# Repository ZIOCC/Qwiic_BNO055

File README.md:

# Zio Qwiic 9DOF IMU BNO055

> This product can be available for purchase [here](https://www.smart-prototyping.com/Zio-9DOF-IMU-BNO055.html).

#### Description

The BNO055 is the ideal orientation solution with low overhead. What that means is that the computational cost is incredibly low for such a high-powered sensor. So, if you have a project consisting of peripherals that demand more computational power, the BNO055 is a great IMU to incorporate.

It provides Absolute Orientation by integrating 3 different sensors: a 3-axis 14-bit accelerometer,  3-axis 16-bit gyroscope, and a 3-axis magnetometer; and outputting the fused data in usable values. 

The following data can be collected by this sensor:

* **Quaternion Absolute Orientation** (4-point quaternion output that is as fast as it is sexy… that’s right, quaternions are sexy.)
* Euler Vector Absolute Orientation ( 3-axis orientation data based on a 360 sphere)
* Linear Acceleration in m/s^2
* Acceleration Vector  in m/s^2
* Magnetic Field Strength Vector
* Gravity Vector
* Angular Velocity Vector
* Temperature

We’ve made this board small enough to be suitable for use in advanced wearables and other space-sensitive projects. It’s been specifically designed for use in projects incorporating Qwiic, and so breaks out only the interrupt pin. However, if you’d like to use it in a non-Qwiic project, just use one of our Qwiic adapters, or you can just take a Qwiic cable, cut off one end, and solder the wire ends to the I2C pins of whatever you want.

Bosch’s smart 9DOF IMU will take raw sensor data and stream out meaningful results at up to 100Hz; you are saved the headache of sifting through algorithms with different levels of accuracy and complexity (and believe you me, they get pretty durned complex). And with the available libraries and example code, you can get it working with your project in a matter of minutes. There is a wide variety of applications in which this board can be used, such as AR, navigation, gaming, fitness, context awareness (think: robotics and mobile devices), and more.

> Note: As with all of the Version 1.0 Zio Qwiic boards, this board has been produced with the I2C pull-ups disconnected by default. If there's a significant length of wire between this board and your MCU, you'll need to solder closed the solder jumpers (labeled SDA, 3v3 and SCL) to connect the pull-up resistors to VCC.

#### Specification

* Accelerometer range: ±2g/±4g/±8g/±16g
* Magnetometer range: ±1300µT (x-, y-axis); ±2500µT (z-axis)
* Gyroscope range:  ±125°/s to ±2000°/s
* Voltage range: 1.7V - 3.6V
* IC: BNO055
* I2C address: 0x28,0x29 (Default: 0x28)
* Dimension with Mounting  Tab: 36.7x14.2 mm
* Dimension without Mounting  Tab: 24.9x14.2mm
* Weight: 1.2g (0.042oz)

#### Links

* [Bosch’s BNO055 Datasheet](https://www.smart-prototyping.com/image/data/NOA-RnD/101892%20BNO%20055/BST_BNO055_DS000_12.pdf)
* [Adafruit BNO055 Arduino Library and Unified Sensor Library](https://github.com/adafruit/Adafruit_BNO055)
* [Adafruit Sensor Library](https://github.com/adafruit/Adafruit_Sensor)
* [Eagle files](https://github.com/ZIOCC/Qwiic_BNO055)

> ###### About Zio
> Zio is a new line of open sourced, compact, and grid layout boards, fully integrated for Arduino and Qwiic ecosystem. Designed ideally for wearables, robotics, small-space limitations or other on the go projects. Check out other awesome Zio products [here](https://www.smart-prototyping.com/Zio).

> All Zio products are released under the [Creative Commons Attribution, Share-Alike License](https://creativecommons.org/licenses/by-sa/4.0/), and in accordance with the principles of the [Open Source Hardware Association's OSHW Statement of Principles 1.0 and OSHW Definition 1.0](https://www.oshwa.org/definition/).

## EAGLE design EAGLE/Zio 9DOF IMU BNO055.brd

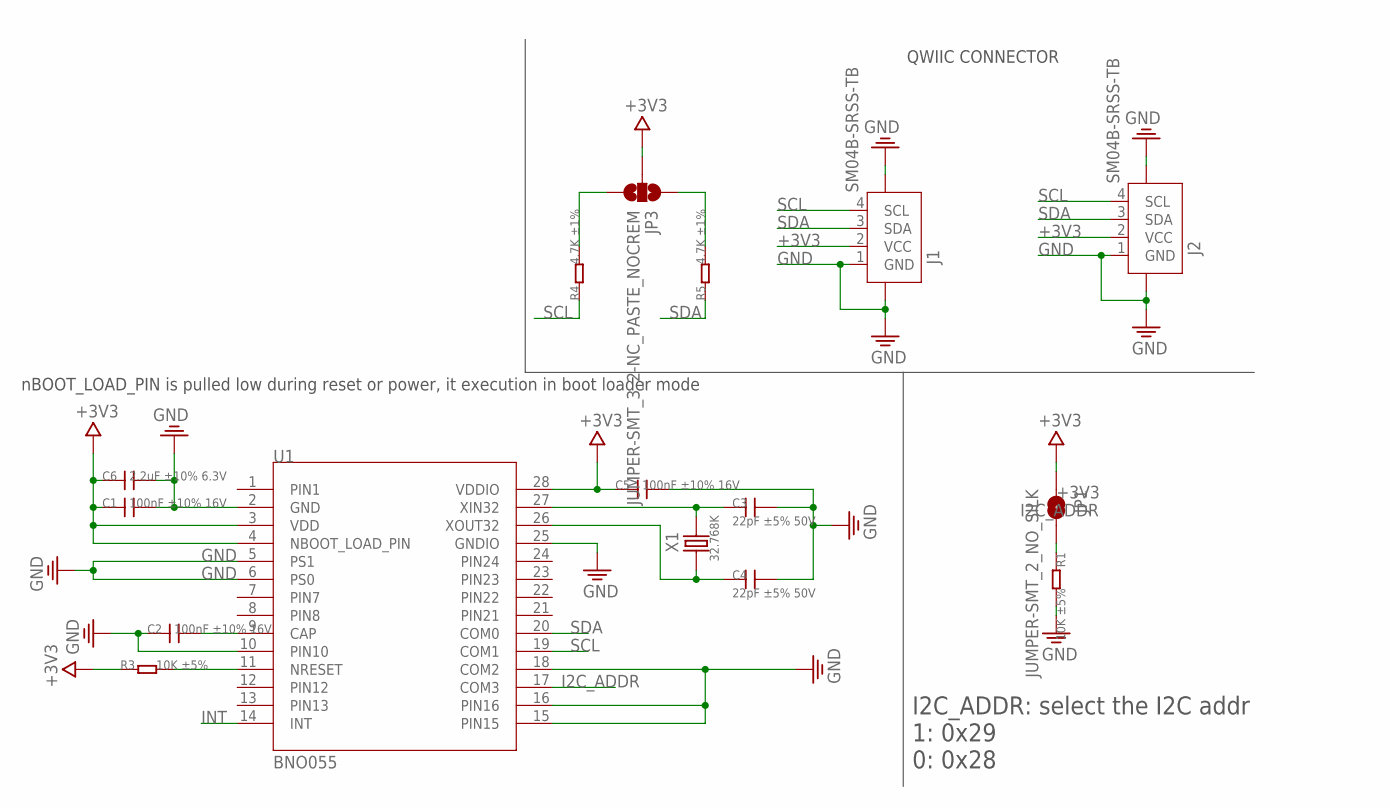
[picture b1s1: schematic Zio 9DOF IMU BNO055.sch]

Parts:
C1, C2, C5: 100nF ±10% 16V; 0402
C3, C4: 22pF ±5% 50V; 0402
C6: 2.2uF ±10% 6.3V; 0402
J1, J2: SM04B-SRSS-TB; JST-SH-4P
JP1: JUMPER-SMT_2_NO_SILK; SMT-JUMPER_2_NO_SILK
JP3: JUMPER-SMT_3_2-NC_PASTE_NOCREM; SMT-JUMPER_3_2-NC_PASTE_SILK_NOCREM
R1, R3: 10K ±5%; 0402
R4, R5: 4.7K ±1%; 0402
U1: BNO055; LGA-28_3.80X5.20/0.5
X1: 32.768K; 2.0X12MM

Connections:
+3V3: C1.1, C5.1, C6.1, J1.2 (VCC), J2.2 (VCC), JP1.1, JP3.2, R3.1, U1.3 (VDD), U1.4 (NBOOT_LOAD_PIN), U1.28 (VDDIO)
GND: C1.2, C2.1, C3.2, C4.2, C5.2, C6.2, J1.1 (GND), J1.NC1 (5), J1.NC2 (6), J2.1 (GND), J2.NC1 (5), J2.NC2 (6), R1.2, U1.2 (GND), U1.5 (PS1), U1.6 (PS0), U1.10 (PIN10), U1.15 (PIN15), U1.16 (PIN16), U1.18 (COM2), U1.25 (GNDIO)
I2C_ADDR: JP1.2, R1.1, U1.17 (COM3)
INT: U1.14 (INT)
unnamed: C2.2, U1.9 (CAP)
unnamed: R3.2, U1.11 (NRESET)
unnamed: C3.1, U1.27 (XIN32), X1.2
unnamed: C4.1, U1.26 (XOUT32), X1.1
unnamed: JP3.3, R4.2
unnamed: JP3.1, R5.2
SCL: J1.4 (SCL), J2.4 (SCL), R4.1, U1.19 (COM1)
SDA: J1.3 (SDA), J2.3 (SDA), R5.1, U1.20 (COM0)

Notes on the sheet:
nBOOT_LOAD_PIN is pulled low during reset or power, it execution in boot loader mode
I2C_ADDR: select the I2C addr 1: 0x29 0: 0x28
QWIIC CONNECTOR

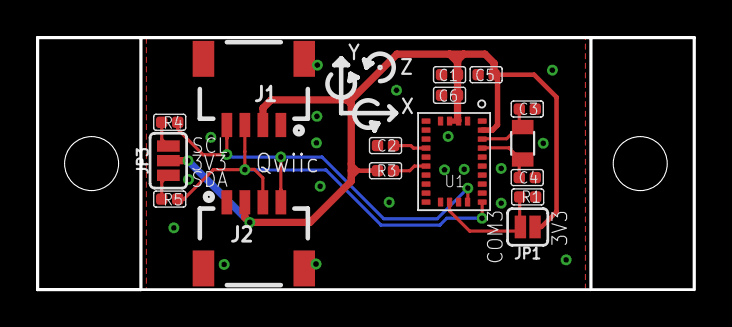
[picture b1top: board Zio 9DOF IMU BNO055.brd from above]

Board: 2 copper layers, 36.5 x 14.0 mm, 19 parts (2 on the bottom side), 11 nets.

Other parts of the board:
E$3: 6MM
LOGO2: LOGO-OSHW-6MILX0070-NT; OSHW_6X70_NOTEXT
U$6: 6MM

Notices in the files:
parts and their libraries:
SparkFun-Jumpers: Licensing: Creative Commons ShareAlike 4.0 International - https://creativecommons.org/licenses/by-sa/4.0
